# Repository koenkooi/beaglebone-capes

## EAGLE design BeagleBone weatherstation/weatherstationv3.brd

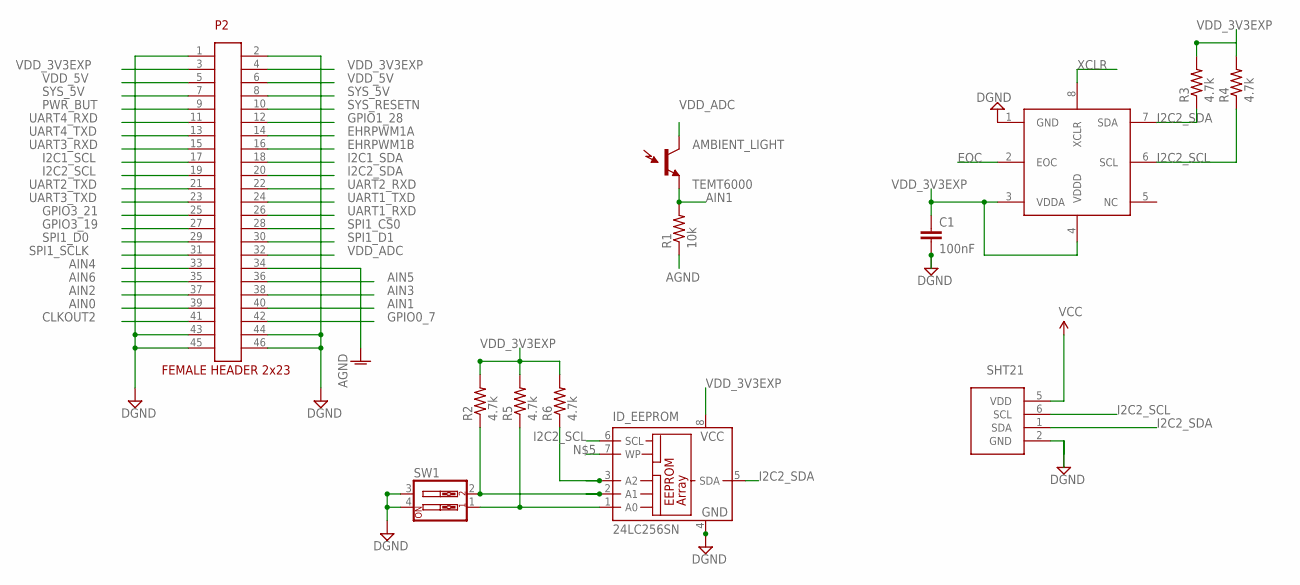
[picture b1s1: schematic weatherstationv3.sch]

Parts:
AMBIENT_LIGHT: TEMT6000; TEMT6000-SEN
BAROMETRIC_PRESSURE: BMP085
C1: 100nF; 0603-CAP
ID_EEPROM: 24LC256SN; SO-08
P2: CONN23-2FB; CONN23-2F
R1: 10k; 0805
R2, R3, R4, R5, R6: 4.7k; 0603-RES
SHT21: SHT21
SW1: SW_DIP-2; DIPSWITCH-02

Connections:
AGND: P2.34, R1.1
AIN0: P2.39
AIN1: AMBIENT_LIGHT.EMITTER (E1), P2.40, R1.2
AIN2: P2.37
AIN3: P2.38
AIN4: P2.33
AIN5: P2.36
AIN6: P2.35
CLKOUT2: P2.41
DGND: BAROMETRIC_PRESSURE.1 (GND), C1.2, ID_EEPROM.4 (GND), P2.1, P2.2, P2.43, P2.44, P2.45, P2.46, SHT21.2 (GND), SW1.3, SW1.4
EHRPWM1A: P2.14
EHRPWM1B: P2.16
EOC: BAROMETRIC_PRESSURE.2 (EOC)
GPIO0_7: P2.42
GPIO1_28: P2.12
GPIO3_19: P2.27
GPIO3_21: P2.25
I2C1_SCL: P2.17
I2C1_SDA: P2.18
I2C2_SCL: BAROMETRIC_PRESSURE.6 (SCL), ID_EEPROM.6 (SCL), P2.19, R4.1, SHT21.6 (SCL)
I2C2_SDA: BAROMETRIC_PRESSURE.7 (SDA), ID_EEPROM.5 (SDA), P2.20, R3.1, SHT21.1 (SDA)
unnamed: ID_EEPROM.1 (A0), R5.1, SW1.1
unnamed: ID_EEPROM.3 (A2), R6.1
unnamed: ID_EEPROM.2 (A1), R2.1, SW1.2
PWR_BUT: P2.9
SPI1_CS0: P2.28
SPI1_D0: P2.29
SPI1_D1: P2.30
SPI1_SCLK: P2.31
SYS_5V: P2.7, P2.8
SYS_RESETN: P2.10
UART1_RXD: P2.26
UART1_TXD: P2.24
UART2_RXD: P2.22
UART2_TXD: P2.21
UART3_RXD: P2.15
UART3_TXD: P2.23
UART4_RXD: P2.11
UART4_TXD: P2.13
VDD_3V3EXP: BAROMETRIC_PRESSURE.3 (VDDA), BAROMETRIC_PRESSURE.4 (VDDD), C1.1, ID_EEPROM.8 (VCC), P2.3, P2.4, R2.2, R3.2, R4.2, R5.2, R6.2, SHT21.5 (VDD)
VDD_5V: P2.5, P2.6
VDD_ADC: AMBIENT_LIGHT.COLLECTOR (C1), P2.32
XCLR: BAROMETRIC_PRESSURE.8 (XCLR)

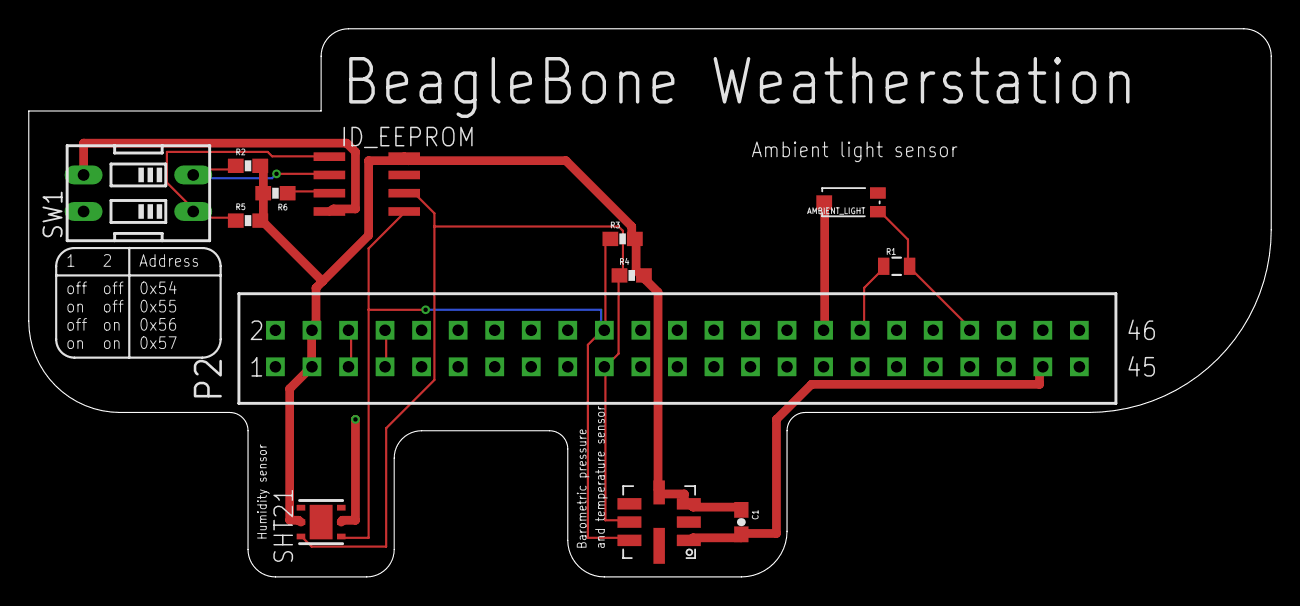
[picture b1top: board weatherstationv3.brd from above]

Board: 2 copper layers, 86.4 x 38.1 mm, 13 parts (0 on the bottom side), 12 nets.

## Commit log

2011-12-12 Beaglebone weatherstation cape: initial commit of EAGLE schematics and layout
2011-12-12 weatherstation: move to subdirectory
2011-12-12 Breadboard: add boardzoo.com EAGLE files
2011-12-13 weatherstation: add gerbers
2011-12-15 weatherstation: Incorporate feedback from Dave
    Schematic:
    * Use consistent names and symbols for signals (e.g DGND)
    * draw dipswitch config differently
    Board:
    * Use a groundplane at the bottom
    * Change power traces to 24mil width
2011-12-15 weatherstation: update gerbers
2011-12-15 weatherstation: tweak board layout to only use vias on power traces
2011-12-15 weatherstation: add PDFs for schematic and layout
2011-12-16 weatherstation: update silkscreen
2011-12-16 weatherstation: add eagleUp files
2011-12-17 weatherstation: add eagleUP attributes
2011-12-17 weatherstation: update eagleUP files
2011-12-21 weatherstation: add v3 of design, this is not a 'cape' but a 'wing'
    The temperature sensitive sensors have moved outside the beaglebone footprint to avoid heating them up with the CPU/FTDI/PMIC
2011-12-21 weatherstation: add gerbers for v3
2011-12-22 weatherstation: add missing EEPROM address pullups into v3 schematic and board
2011-12-22 weatherstation: update v3 gerbers
2011-12-22 weatherstation: fix typo reported by Steve Sakoman, move EEPROM pullups around
2011-12-24 weatherstation: cut away some more PCB around the sensors
